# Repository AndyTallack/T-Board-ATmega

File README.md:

T-Board-ATMega
==============

T-Board for use on Breadboard - ATMega 328

This is a series of boards to speed up development of your own standalone ATMega/ATTiny projects.  The T-Board houses the microprocessor, power-supply and FTDI interface, with a breadboard-compatible footprint.  This allows you to get up and running fast with the core ATMega/ATTiny "heart" of your project.

This board is based on the great Arduino concept, and is compatible with the Arduino IDE.  It differs in that it:
- allows you to switch between 3.3V and 5V
- allows you to select crystals for low-power applications
- fits snugly into a breadboard, keeping your project together

There are 2 sets of schematic:
- T-Board-328 Etch:	1-layer, for hand-etching.  No ICSP header
- T-Board-328 PCB:	2-layer, for production-house.  With ICSP header

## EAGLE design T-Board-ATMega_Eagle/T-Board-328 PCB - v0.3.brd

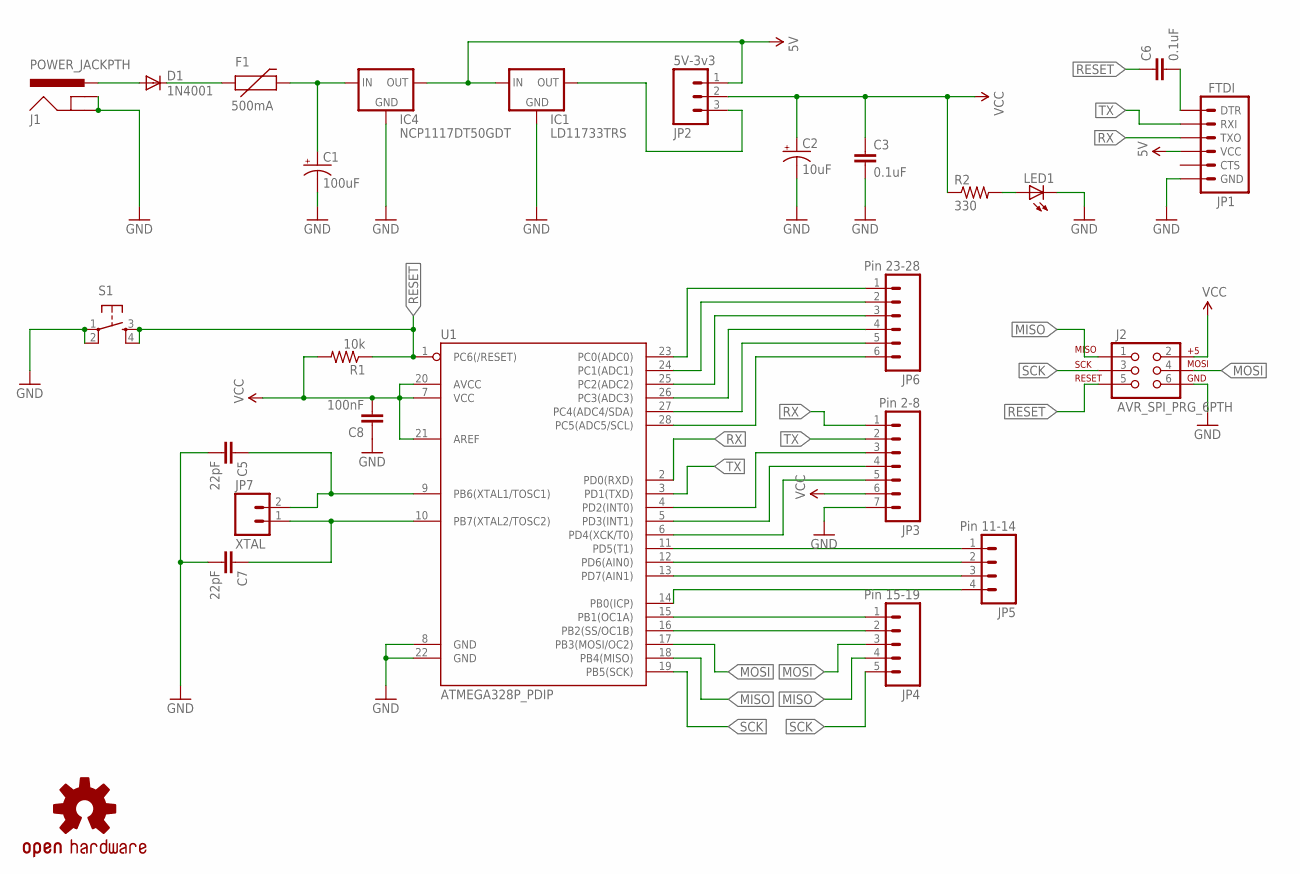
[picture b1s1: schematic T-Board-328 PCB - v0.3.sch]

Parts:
C1: 100uF; CPOL-RADIAL-100UF-25V
C2: 10uF; CPOL-RADIAL-10UF-25V
C3, C6: 0.1uF; 1206
C5, C7: 22pF; 1206
C8: 100nF; 1206
D1: 1N4001; DIODE-1N4001
F1: 500mA; PTC
IC1: LD11733TRS; SOT223
IC4: NCP1117DT50GDT; DPACK
J1: POWER_JACKPTH; POWER_JACK_PTH
J2: AVR_SPI_PRG_6PTH; 2X3
JP1: FTDI; 1X06_LONGPADS
JP2: 5V-3v3; 1X03
JP3: Pin 2-8; 1X07
JP4: Pin 15-19; 1X05
JP5: Pin 11-14; 1X04
JP6: Pin 23-28; 1X06
JP7: XTAL; 1X02
LED1: LED1206; LED-1206
LOGO1: OSHW-LOGOS; OSHW-LOGO-S
R1: 10k; 1206
R2: 330; 1206
S1: TAC_SWITCHPTH; TACTILE-PTH
U1: ATMEGA328P_PDIP; DIL28-3

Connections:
5V: IC1.3 (IN), IC4.4 (OUT), JP1.4 (VCC), JP2.1
GND: C1.2 (-), C2.2 (-), C3.2, C5.2, C7.2, C8.1, IC1.1 (GND), IC4.1 (GND), J1.GND, J1.GNDBREAK, J2.6, JP1.6 (GND), JP3.7, LED1.C, S1.1, S1.2, U1.8 (GND), U1.22 (GND)
MISO: J2.1, JP4.4, U1.18 (PB4(MISO))
MOSI: J2.4, JP4.3, U1.17 (PB3(MOSI/OC2))
unnamed: D1.A, J1.PWR
unnamed: JP6.1, U1.23 (PC0(ADC0))
unnamed: D1.C, F1.P$1 (1)
unnamed: C1.1 (+), F1.P$2 (2), IC4.3 (IN)
unnamed: JP6.2, U1.24 (PC1(ADC1))
unnamed: C6.2, JP1.1 (DTR)
unnamed: C7.1, JP7.1, U1.10 (PB7(XTAL2/TOSC2))
unnamed: C5.1, JP7.2, U1.9 (PB6(XTAL1/TOSC1))
unnamed: LED1.A, R2.2
unnamed: IC1.4 (OUT), JP2.3
unnamed: JP5.1, U1.11 (PD5(T1))
unnamed: JP5.2, U1.12 (PD6(AIN0))
unnamed: JP5.3, U1.13 (PD7(AIN1))
unnamed: JP5.4, U1.14 (PB0(ICP))
unnamed: JP4.1, U1.15 (PB1(OC1A))
unnamed: JP4.2, U1.16 (PB2(SS/OC1B))
unnamed: JP6.3, U1.25 (PC2(ADC2))
unnamed: JP6.4, U1.26 (PC3(ADC3))
unnamed: JP6.5, U1.27 (PC4(ADC4/SDA))
unnamed: JP6.6, U1.28 (PC5(ADC5/SCL))
unnamed: JP3.3, U1.4 (PD2(INT0))
unnamed: JP3.4, U1.5 (PD3(INT1))
unnamed: JP3.5, U1.6 (PD4(XCK/T0))
RESET: C6.1, J2.5, R1.1, S1.3, S1.4, U1.1 (PC6(/RESET))
RX: JP1.3 (TXO), JP3.1, U1.2 (PD0(RXD))
SCK: J2.3, JP4.5, U1.19 (PB5(SCK))
TX: JP1.2 (RXI), JP3.2, U1.3 (PD1(TXD))
VCC: C2.1 (+), C3.1, C8.2, J2.2, JP2.2, JP3.6, R1.2, R2.1, U1.7 (VCC), U1.20 (AVCC), U1.21 (AREF)

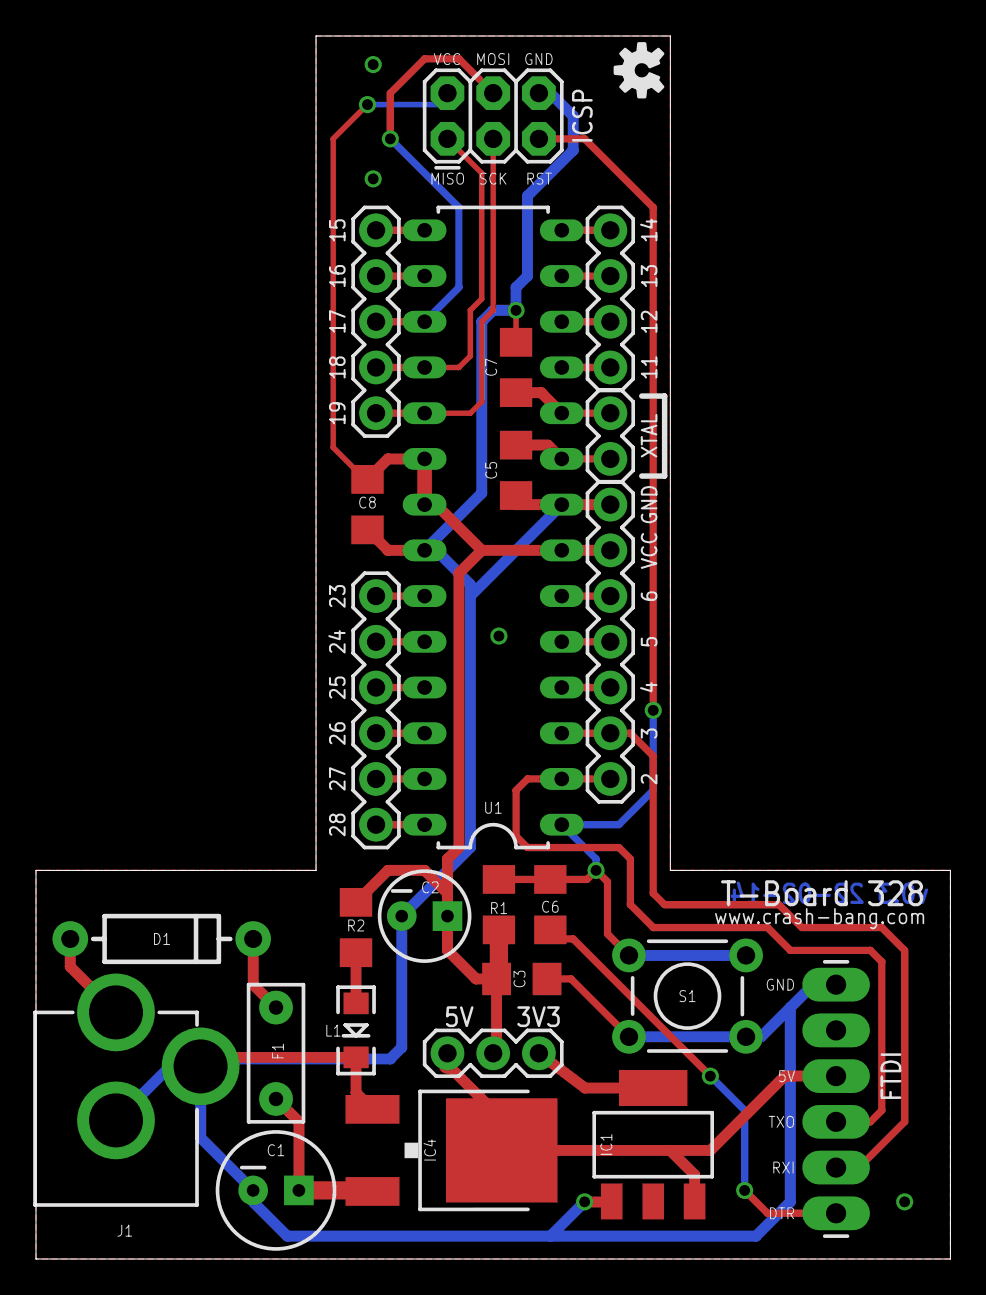
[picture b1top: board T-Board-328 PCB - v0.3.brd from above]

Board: 2 copper layers, 50.8 x 67.9 mm, 26 parts (0 on the bottom side), 32 nets.

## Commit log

2014-02-14 v0.3 - First pre-release
2014-03-16 v0.4 - Second Prototype
    Second prototype sent to OSHPark for fab.
    - Reduced footprint
    - Corrected mirrored voltage regulators
    - Corrected unconnected capacitor
2014-04-11 Adjusted header pins
    Header pins spacing corrected to fit breadboard more precisely
2015-02-17 Corrected License to CCA-BY-SA

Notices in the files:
parts and their libraries:
SparkFun-DigitalIC: Licensing: CC v3.0 Share-Alike You are welcome to use this library for commercial purposes.
